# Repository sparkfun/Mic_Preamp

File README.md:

Mic_Preamp
==========
[
*SparkFun Mic Preamp (PRT-08872)*](https://www.sparkfun.com/products/8872)

This breakout is a simple microphone preamp circuit for a wide range of microphone types. 
It enables you to attach mics to your larger stereo amplifier.

Repository Contents
-------------------
* **/Hardware** - All Eagle design files (.brd, .sch)

License Information
-------------------
The hardware is released under [Creative Commons ShareAlike 4.0 International](https://creativecommons.org/licenses/by-sa/4.0/).

Distributed as-is; no warranty is given.

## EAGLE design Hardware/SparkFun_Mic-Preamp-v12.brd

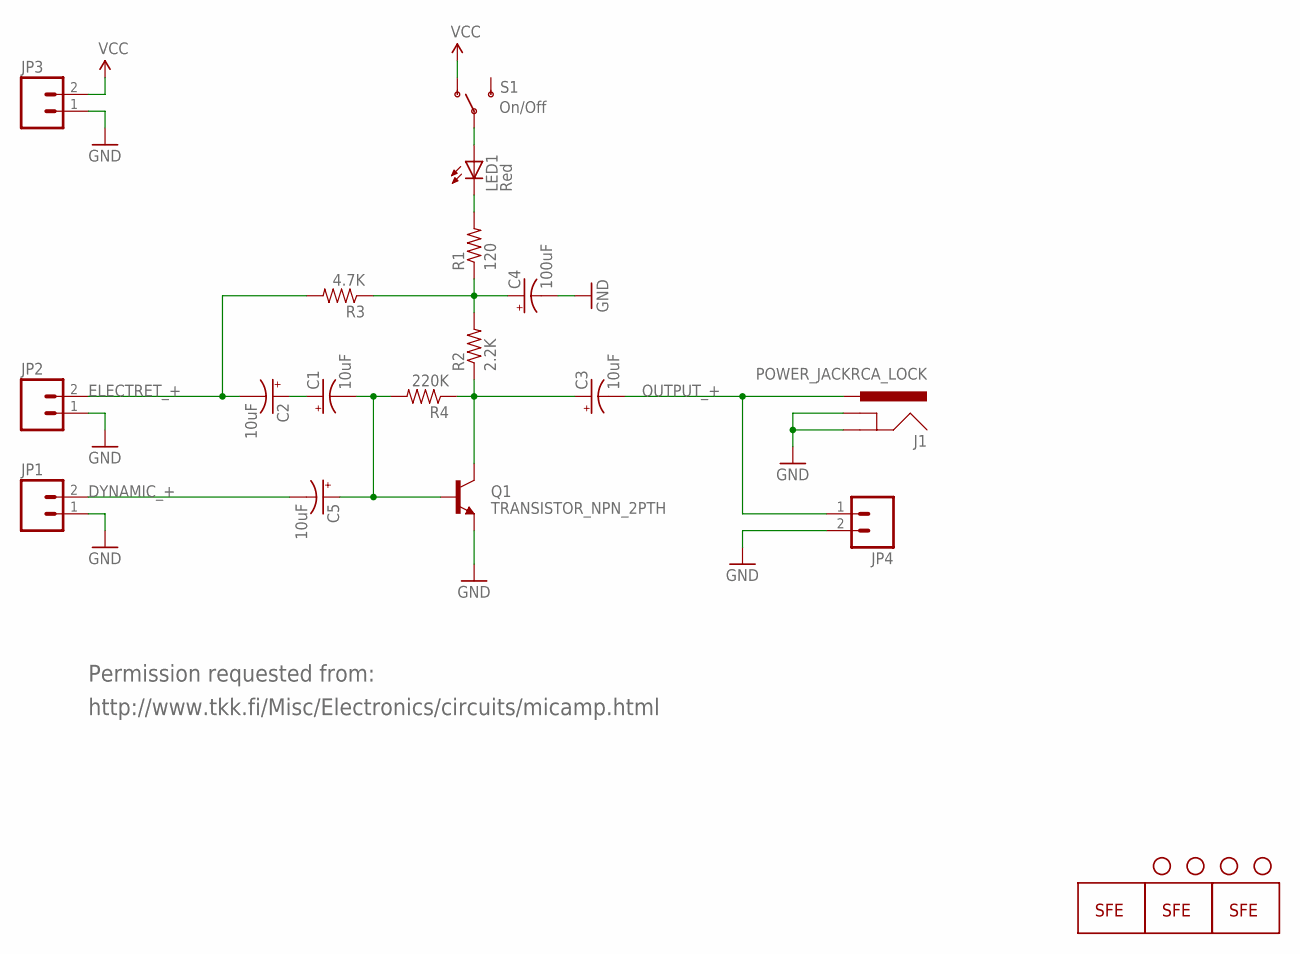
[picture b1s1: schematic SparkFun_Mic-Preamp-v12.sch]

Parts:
C1, C2, C3, C5: 10uF; CPOL-RADIAL-10UF-25V
C4: 100uF; CPOL-RADIAL-100UF-25V
J1: POWER_JACKRCA_LOCK; RCA_LOCK
JP1, JP2, JP3, JP4: M02PTH; 1X02
JP6: LOGO-SFENW2; SFE-NEW-WEB
LED1: Red; LED5MM
Q1: TRANSISTOR_NPN_2PTH; TO-92
R1: 120; AXIAL-0.3
R2: 2.2K; AXIAL-0.3
R3: 4.7K; AXIAL-0.3
R4: 220K; AXIAL-0.3
S1: On/Off; SWITCH-SPDT_LOCK.007S
U$1, U$6: LOGO-SFESK; SFE-LOGO-FLAME
U$2, U$3, U$4, U$5: STAND-OFF

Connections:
DYNAMIC_+: C5.2 (-), JP1.2
ELECTRET_+: C2.2 (-), JP2.2, R3.P$2 (2)
GND: C4.2 (-), J1.BARREL (GND), J1.SPRING (GNDBREAK), JP1.1, JP2.1, JP3.1, JP4.2, Q1.3 (E)
unnamed: LED1.K (C), R1.P$2 (2)
unnamed: C3.1 (+), Q1.1 (C), R2.P$1 (1), R4.P$1 (1)
unnamed: C4.1 (+), R1.P$1 (1), R2.P$2 (2), R3.P$1 (1)
unnamed: C1.2 (-), C5.1 (+), Q1.2 (B), R4.P$2 (2)
unnamed: C1.1 (+), C2.1 (+)
unnamed: LED1.A, S1.2
OUTPUT_+: C3.2 (-), J1.BREAK (PWR), JP4.1
VCC: JP3.2, S1.1 (O)

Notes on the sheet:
http://www.tkk.fi/Misc/Electronics/circuits/micamp.html
Permission requested from:

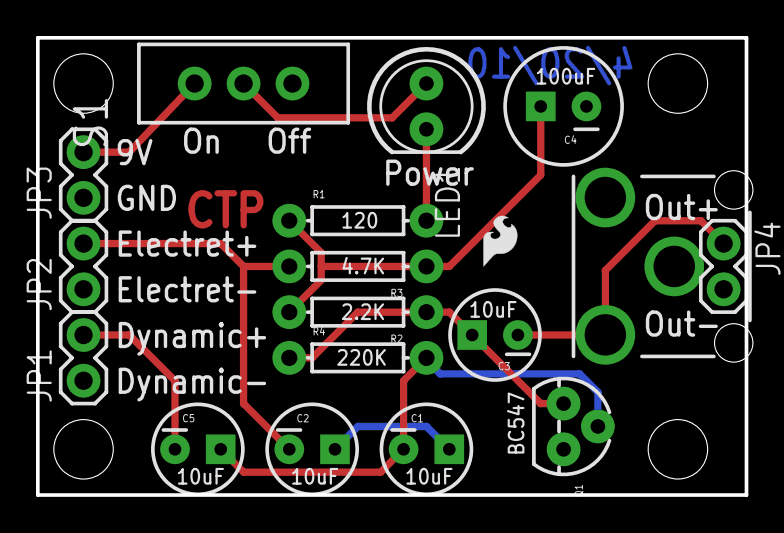
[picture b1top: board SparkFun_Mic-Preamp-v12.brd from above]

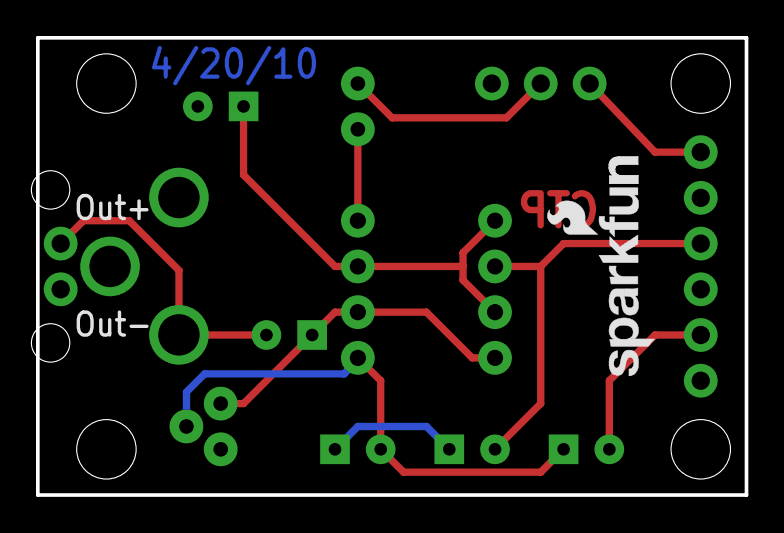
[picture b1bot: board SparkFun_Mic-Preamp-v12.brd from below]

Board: 2 copper layers, 39.4 x 25.4 mm, 24 parts (2 on the bottom side), 11 nets.

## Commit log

2015-01-06 Initial hardware commit
